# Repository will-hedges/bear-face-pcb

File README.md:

# Cortex Face
 v1 of my QMK-compatible replacement PCB for the Vortex Race 3, hilariously named after my boi

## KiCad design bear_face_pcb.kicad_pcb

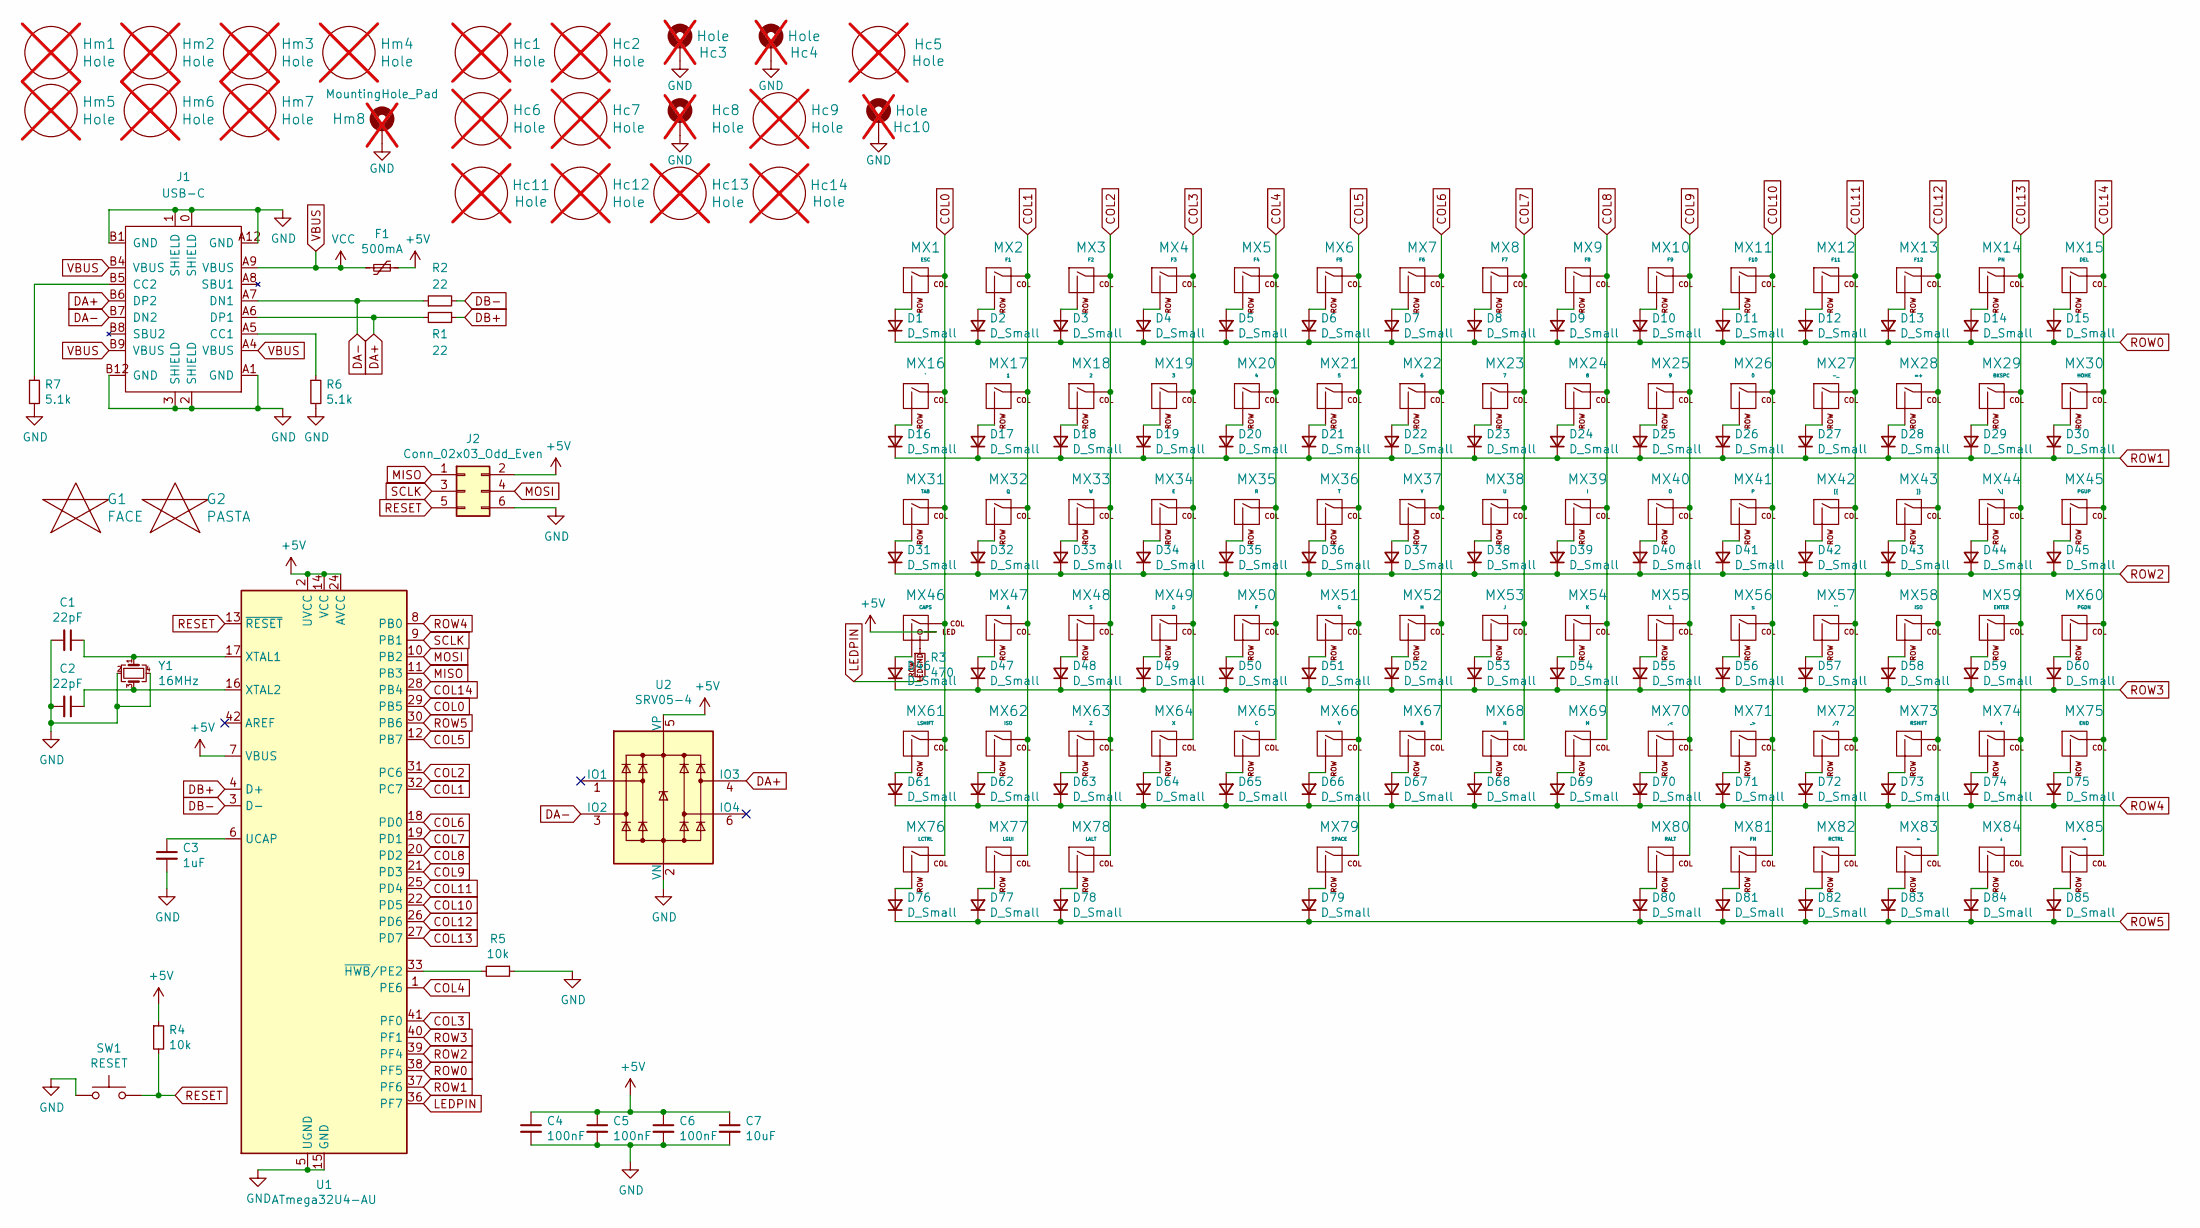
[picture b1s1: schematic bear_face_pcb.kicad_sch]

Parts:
C1, C2: 22pF; C_0805_2012Metric; LCSC C1804
C3: 1uF; C_0805_2012Metric; LCSC C28323
C4, C5, C6: 100nF; C_0805_2012Metric; LCSC C49678
C7: 10uF; C_0805_2012Metric; LCSC C15850
D1, D2, D3, D4, D5, D6, D7, D8, D9, D10, D11, D12, D13, D14, D15, D16, D17, D18, D19, D20, D21, D22, D23, D24, D25, D26, D27, D28, D29, D30, D31, D32, D33, D34, D35, D36, D37, D38, D39, D40, D41, D42, D43, D44, D45, D46, D47, D48, D49, D50, D51, D52, D53, D54, D55, D56, D57, D58, D59, D60, D61, D62, D63, D64, D65, D66, D67, D68, D69, D70, D71, D72, D73, D74, D75, D76, D77, D78, D79, D80, D81, D82, D83, D84, D85: D_Small; D_SOD-123; LCSC C81598
F1: 500mA; Fuse_1206_3216Metric; LCSC C70076
G1: FACE; cbf_small_flipped
G2: PASTA; pasta_small
Hc1, Hc2, Hc5, Hc6, Hc7, Hc9, Hc11, Hc12, Hc13, Hc14: Hole; MountingHole_6mm; not fitted
Hc3, Hc4, Hc8, Hc10: Hole; MountingHole_2.2mm_M2_Pad; not fitted
Hm1, Hm2, Hm3, Hm4, Hm5, Hm6, Hm7: Hole; MountingHole_6mm; not fitted
Hm8: MountingHole_Pad; MountingHole_Header_Pin_Pad; not fitted
J1: USB-C; USB-C_SMD-TYPE-C-31-M-12; LCSC C165948
J2: Conn_02x03_Odd_Even; 2x3pinsocketOFFSET
MX1: ESC; MXOnly-1.5U-NoLED
MX2: F1; MXOnly-1U-NoLED
MX3: F2; MXOnly-1U-NoLED
MX4: F3; MXOnly-1U-NoLED
MX5: F4; MXOnly-1U-NoLED
MX6: F5; MXOnly-1U-NoLED
MX7: F6; MXOnly-1U-NoLED
MX8: F7; MXOnly-1U-NoLED
MX9: F8; MXOnly-1U-NoLED
MX10: F9; MXOnly-1U-NoLED
MX11: F10; MXOnly-1U-NoLED
MX12: F11; MXOnly-1U-NoLED
MX13: F12; MXOnly-1U-NoLED
MX14: PN; MXOnly-1U-NoLED
MX15: DEL; MXOnly-1.5U-NoLED
MX16: `; MXOnly-1U-NoLED
MX17: 1; MXOnly-1U-NoLED
MX18: 2; MXOnly-1U-NoLED
MX19: 3; MXOnly-1U-NoLED
MX20: 4; MXOnly-1U-NoLED
MX21: 5; MXOnly-1U-NoLED
MX22: 6; MXOnly-1U-NoLED
MX23: 7; MXOnly-1U-NoLED
MX24: 8; MXOnly-1U-NoLED
MX25: 9; MXOnly-1U-NoLED
MX26: 0; MXOnly-1U-NoLED
MX27: -_; MXOnly-1U-NoLED
MX28: =+; MXOnly-1U-NoLED
MX29: BKSPC; MXOnly-2U-NoLED
MX30: HOME; MXOnly-1U-NoLED
MX31: TAB; MXOnly-1.5U-NoLED
MX32: Q; MXOnly-1U-NoLED
MX33: W; MXOnly-1U-NoLED
MX34: E; MXOnly-1U-NoLED
MX35: R; MXOnly-1U-NoLED
MX36: T; MXOnly-1U-NoLED
MX37: Y; MXOnly-1U-NoLED
MX38: U; MXOnly-1U-NoLED
MX39: I; MXOnly-1U-NoLED
MX40: O; MXOnly-1U-NoLED
MX41: P; MXOnly-1U-NoLED
MX42: [{; MXOnly-1U-NoLED
MX43: ]}; MXOnly-1U-NoLED
MX44: \|; MXOnly-1.5U-NoLED
MX45: PGUP; MXOnly-1U-NoLED
MX46: CAPS; MXOnly-Stepped-Caps-XD75
MX47: A; MXOnly-1U-NoLED
MX48: S; MXOnly-1U-NoLED
MX49: D; MXOnly-1U-NoLED
MX50: F; MXOnly-1U-NoLED
MX51: G; MXOnly-1U-NoLED
MX52: H; MXOnly-1U-NoLED
MX53: J; MXOnly-1U-NoLED
MX54: K; MXOnly-1U-NoLED
MX55: L; MXOnly-1U-NoLED
MX56: ;:; MXOnly-1U-NoLED
MX57: '"; MXOnly-1U-NoLED
MX58, MX62: ISO; MXOnly-1U-NoLED
MX59: ENTER; MXOnly-ISO-ANSI-Enter-ReversedStabilizers
MX60: PGDN; MXOnly-1U-NoLED
MX61: LSHIFT; MXOnly-Split-LShift
MX63: Z; MXOnly-1U-NoLED
MX64: X; MXOnly-1U-NoLED
MX65: C; MXOnly-1U-NoLED
MX66: V; MXOnly-1U-NoLED
MX67: B; MXOnly-1U-NoLED
MX68: N; MXOnly-1U-NoLED
MX69: M; MXOnly-1U-NoLED
MX70: ,<; MXOnly-1U-NoLED
MX71: .>; MXOnly-1U-NoLED
MX72: /?; MXOnly-1U-NoLED
MX73: RSHIFT; MXOnly-1.75U-NoLED
MX74: ↑; MXOnly-1U-NoLED
MX75: END; MXOnly-1U-NoLED
MX76: LCTRL; MXOnly-1.25U-NoLED
MX77: LGUI; MXOnly-1.25U-NoLED
MX78: LALT; MXOnly-1.25U-NoLED
MX79: SPACE; MXOnly-6.25U-ReversedStabilizers-NoLED
MX80: RALT; MXOnly-1U-NoLED
MX81: FN; MXOnly-1U-NoLED
MX82: RCTRL; MXOnly-1U-NoLED
MX83: ←; MXOnly-1U-NoLED
MX84: ↓; MXOnly-1U-NoLED
MX85: →; MXOnly-1U-NoLED
R1, R2: 22; R_0805_2012Metric; LCSC C17561
R3: 470; R_0805_2012Metric; LCSC C17710
R4, R5: 10k; R_0805_2012Metric; LCSC C17414
R6, R7: 5.1k; R_0805_2012Metric; LCSC C27834
SW1: RESET; 6x6mm_RESET
U1: ATmega32U4-AU; ATMEGA32U4-AU; LCSC C44854
U2: SRV05-4; SOT-23-6; LCSC C85364
Y1: 16MHz; Crystal_SMD_3225-4Pin_3.2x2.5mm; LCSC C13738

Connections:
+5V: C4.1, C5.1, C6.1, C7.1, F1.1, J2.2, MX46.3 (LED), R4.1, U1.2 (UVCC), U1.7 (VBUS), U1.14 (VCC), U1.24 (AVCC), U1.34 (VCC), U1.44 (AVCC), U2.5 (VP)
COL0: MX1.1 (COL), MX16.1 (COL), MX31.1 (COL), MX46.1 (COL), MX61.1 (COL), MX76.1 (COL), U1.29 (PB5)
COL1: MX2.1 (COL), MX17.1 (COL), MX32.1 (COL), MX47.1 (COL), MX62.1 (COL), MX77.1 (COL), U1.32 (PC7)
COL2: MX3.1 (COL), MX18.1 (COL), MX33.1 (COL), MX48.1 (COL), MX63.1 (COL), MX78.1 (COL), U1.31 (PC6)
COL3: MX4.1 (COL), MX19.1 (COL), MX34.1 (COL), MX49.1 (COL), MX64.1 (COL), U1.41 (PF0)
COL4: MX5.1 (COL), MX20.1 (COL), MX35.1 (COL), MX50.1 (COL), MX65.1 (COL), U1.1 (PE6)
COL5: MX6.1 (COL), MX21.1 (COL), MX36.1 (COL), MX51.1 (COL), MX66.1 (COL), MX79.1 (COL), U1.12 (PB7)
COL6: MX7.1 (COL), MX22.1 (COL), MX37.1 (COL), MX52.1 (COL), MX67.1 (COL), U1.18 (PD0)
COL7: MX8.1 (COL), MX23.1 (COL), MX38.1 (COL), MX53.1 (COL), MX68.1 (COL), U1.19 (PD1)
COL8: MX9.1 (COL), MX24.1 (COL), MX39.1 (COL), MX54.1 (COL), MX69.1 (COL), U1.20 (PD2)
COL9: MX10.1 (COL), MX25.1 (COL), MX40.1 (COL), MX55.1 (COL), MX70.1 (COL), MX80.1 (COL), U1.21 (PD3)
COL10: MX11.1 (COL), MX26.1 (COL), MX41.1 (COL), MX56.1 (COL), MX71.1 (COL), MX81.1 (COL), U1.22 (PD5)
COL11: MX12.1 (COL), MX27.1 (COL), MX42.1 (COL), MX57.1 (COL), MX72.1 (COL), MX82.1 (COL), U1.25 (PD4)
COL12: MX13.1 (COL), MX28.1 (COL), MX43.1 (COL), MX58.1 (COL), MX73.1 (COL), MX83.1 (COL), U1.26 (PD6)
COL13: MX14.1 (COL), MX29.1 (COL), MX44.1 (COL), MX59.1 (COL), MX74.1 (COL), MX84.1 (COL), U1.27 (PD7)
COL14: MX15.1 (COL), MX30.1 (COL), MX45.1 (COL), MX60.1 (COL), MX75.1 (COL), MX85.1 (COL), U1.28 (PB4)
DA+: J1.A6 (DP1), J1.B6 (DP2), R1.2, U2.4 (IO3)
DA-: J1.A7 (DN1), J1.B7 (DN2), R2.1, U2.3 (IO2)
DB+: R1.1, U1.4 (D+)
DB-: R2.2, U1.3 (D-)
GND: C1.2, C2.2, C3.2, C4.2, C5.2, C6.2, C7.2, Hc3.1, Hc4.1, Hc8.1, Hc10.1, Hm8.1, J1.0 (SHIELD), J1.1 (SHIELD), J1.2 (SHIELD), J1.3 (SHIELD), J1.A1 (GND), J1.A12 (GND), J1.B1 (GND), J1.B12 (GND), J2.6, R5.1, R6.2, R7.2, SW1.1, U1.5 (UGND), U1.15 (GND), U1.23 (GND), U1.35 (GND), U1.43 (GND), U2.2 (VN), Y1.2, Y1.4
LEDPIN: R3.2, U1.36 (PF7)
MISO: J2.1, U1.11 (PB3)
MOSI: J2.4, U1.10 (PB2)
unnamed: D1.2 (A), MX1.2 (ROW)
unnamed: D2.2 (A), MX2.2 (ROW)
unnamed: D3.2 (A), MX3.2 (ROW)
unnamed: D4.2 (A), MX4.2 (ROW)
unnamed: D5.2 (A), MX5.2 (ROW)
unnamed: D6.2 (A), MX6.2 (ROW)
unnamed: D7.2 (A), MX7.2 (ROW)
unnamed: D8.2 (A), MX8.2 (ROW)
unnamed: D9.2 (A), MX9.2 (ROW)
unnamed: D10.2 (A), MX10.2 (ROW)
unnamed: D11.2 (A), MX11.2 (ROW)
unnamed: D12.2 (A), MX12.2 (ROW)
unnamed: D13.2 (A), MX13.2 (ROW)
unnamed: D14.2 (A), MX14.2 (ROW)
unnamed: D15.2 (A), MX15.2 (ROW)
unnamed: D16.2 (A), MX16.2 (ROW)
unnamed: D17.2 (A), MX17.2 (ROW)
unnamed: D18.2 (A), MX18.2 (ROW)
unnamed: D19.2 (A), MX19.2 (ROW)
unnamed: D20.2 (A), MX20.2 (ROW)
unnamed: D21.2 (A), MX21.2 (ROW)
unnamed: D22.2 (A), MX22.2 (ROW)
unnamed: D23.2 (A), MX23.2 (ROW)
unnamed: D24.2 (A), MX24.2 (ROW)
unnamed: D25.2 (A), MX25.2 (ROW)
unnamed: D26.2 (A), MX26.2 (ROW)
unnamed: D27.2 (A), MX27.2 (ROW)
unnamed: D28.2 (A), MX28.2 (ROW)
unnamed: D29.2 (A), MX29.2 (ROW)
unnamed: D30.2 (A), MX30.2 (ROW)
unnamed: D31.2 (A), MX31.2 (ROW)
unnamed: D32.2 (A), MX32.2 (ROW)
unnamed: D33.2 (A), MX33.2 (ROW)
unnamed: D34.2 (A), MX34.2 (ROW)
unnamed: D35.2 (A), MX35.2 (ROW)
unnamed: D36.2 (A), MX36.2 (ROW)
unnamed: D37.2 (A), MX37.2 (ROW)
unnamed: D38.2 (A), MX38.2 (ROW)
unnamed: D39.2 (A), MX39.2 (ROW)
unnamed: D40.2 (A), MX40.2 (ROW)
unnamed: D41.2 (A), MX41.2 (ROW)
unnamed: D42.2 (A), MX42.2 (ROW)
unnamed: D43.2 (A), MX43.2 (ROW)
unnamed: D44.2 (A), MX44.2 (ROW)
unnamed: D45.2 (A), MX45.2 (ROW)
unnamed: D46.2 (A), MX46.2 (ROW)
unnamed: D47.2 (A), MX47.2 (ROW)
unnamed: D48.2 (A), MX48.2 (ROW)
unnamed: D49.2 (A), MX49.2 (ROW)
unnamed: D50.2 (A), MX50.2 (ROW)
unnamed: D51.2 (A), MX51.2 (ROW)
unnamed: D52.2 (A), MX52.2 (ROW)
unnamed: D53.2 (A), MX53.2 (ROW)
unnamed: D54.2 (A), MX54.2 (ROW)
unnamed: D55.2 (A), MX55.2 (ROW)
unnamed: D56.2 (A), MX56.2 (ROW)
unnamed: D57.2 (A), MX57.2 (ROW)
unnamed: D58.2 (A), MX58.2 (ROW)
unnamed: D59.2 (A), MX59.2 (ROW)
unnamed: D60.2 (A), MX60.2 (ROW)
unnamed: D61.2 (A), MX61.2 (ROW)
unnamed: D62.2 (A), MX62.2 (ROW)
unnamed: D63.2 (A), MX63.2 (ROW)
unnamed: D64.2 (A), MX64.2 (ROW)
unnamed: D65.2 (A), MX65.2 (ROW)
unnamed: D66.2 (A), MX66.2 (ROW)
unnamed: D67.2 (A), MX67.2 (ROW)
unnamed: D68.2 (A), MX68.2 (ROW)
unnamed: D69.2 (A), MX69.2 (ROW)
unnamed: D70.2 (A), MX70.2 (ROW)
unnamed: D71.2 (A), MX71.2 (ROW)
unnamed: D72.2 (A), MX72.2 (ROW)
unnamed: D73.2 (A), MX73.2 (ROW)
unnamed: D74.2 (A), MX74.2 (ROW)
unnamed: D75.2 (A), MX75.2 (ROW)
unnamed: D76.2 (A), MX76.2 (ROW)
unnamed: D77.2 (A), MX77.2 (ROW)
unnamed: D78.2 (A), MX78.2 (ROW)
unnamed: D79.2 (A), MX79.2 (ROW)
unnamed: D80.2 (A), MX80.2 (ROW)
unnamed: D81.2 (A), MX81.2 (ROW)
unnamed: D82.2 (A), MX82.2 (ROW)
unnamed: D83.2 (A), MX83.2 (ROW)
unnamed: D84.2 (A), MX84.2 (ROW)
unnamed: D85.2 (A), MX85.2 (ROW)
unnamed: J1.A5 (CC1), R6.1
unnamed: J1.B5 (CC2), R7.1
unnamed: MX46.4 (LEDGND), R3.1
unnamed: C3.1, U1.6 (UCAP)
unnamed: C1.1, U1.17 (XTAL1), Y1.1
unnamed: C2.1, U1.16 (XTAL2), Y1.3
unnamed: R5.2, U1.33 (~HWB/PE2)
RESET: J2.5, R4.2, SW1.2, U1.13 (~RESET)
ROW0: D1.1 (K), D2.1 (K), D3.1 (K), D4.1 (K), D5.1 (K), D6.1 (K), D7.1 (K), D8.1 (K), D9.1 (K), D10.1 (K), D11.1 (K), D12.1 (K), D13.1 (K), D14.1 (K), D15.1 (K), U1.38 (PF5)
ROW1: D16.1 (K), D17.1 (K), D18.1 (K), D19.1 (K), D20.1 (K), D21.1 (K), D22.1 (K), D23.1 (K), D24.1 (K), D25.1 (K), D26.1 (K), D27.1 (K), D28.1 (K), D29.1 (K), D30.1 (K), U1.37 (PF6)
ROW2: D31.1 (K), D32.1 (K), D33.1 (K), D34.1 (K), D35.1 (K), D36.1 (K), D37.1 (K), D38.1 (K), D39.1 (K), D40.1 (K), D41.1 (K), D42.1 (K), D43.1 (K), D44.1 (K), D45.1 (K), U1.39 (PF4)
ROW3: D46.1 (K), D47.1 (K), D48.1 (K), D49.1 (K), D50.1 (K), D51.1 (K), D52.1 (K), D53.1 (K), D54.1 (K), D55.1 (K), D56.1 (K), D57.1 (K), D58.1 (K), D59.1 (K), D60.1 (K), U1.40 (PF1)
ROW4: D61.1 (K), D62.1 (K), D63.1 (K), D64.1 (K), D65.1 (K), D66.1 (K), D67.1 (K), D68.1 (K), D69.1 (K), D70.1 (K), D71.1 (K), D72.1 (K), D73.1 (K), D74.1 (K), D75.1 (K), U1.8 (PB0)
ROW5: D76.1 (K), D77.1 (K), D78.1 (K), D79.1 (K), D80.1 (K), D81.1 (K), D82.1 (K), D83.1 (K), D84.1 (K), D85.1 (K), U1.30 (PB6)
SCLK: J2.3, U1.9 (PB1)
VBUS: F1.2, J1.A4 (VBUS), J1.A9 (VBUS), J1.B4 (VBUS), J1.B9 (VBUS)

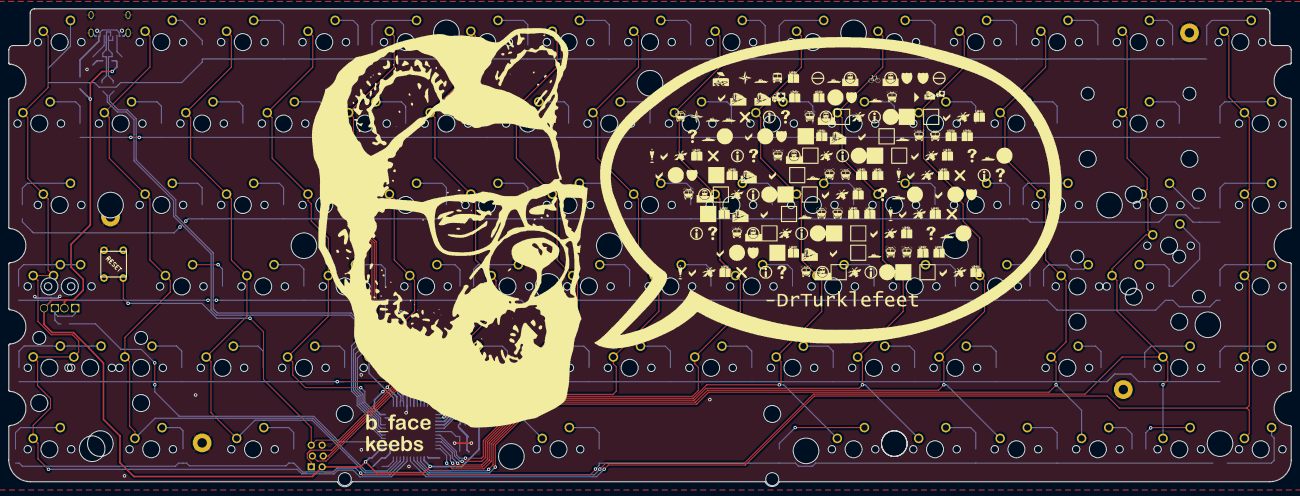
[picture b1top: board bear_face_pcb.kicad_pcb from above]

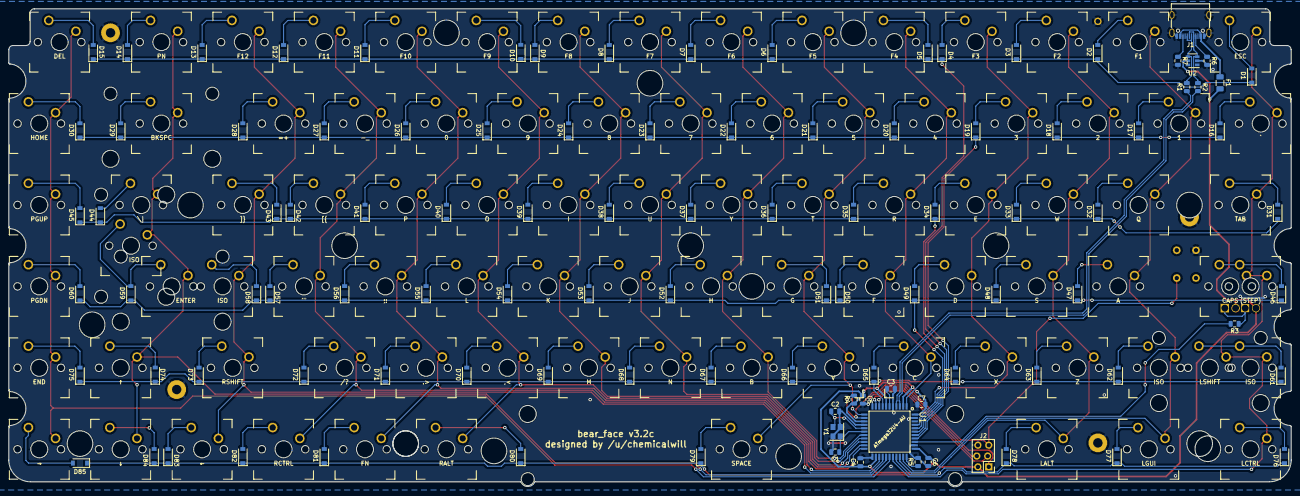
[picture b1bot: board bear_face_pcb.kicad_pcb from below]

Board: 2 copper layers, 300.0 x 111.8 mm, 215 parts (104 on the bottom side), 125 nets.

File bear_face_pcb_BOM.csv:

Comment,Designator,Footprint,LCSC
"22pF","C1,C2","Capacitor_SMD:C_0805_2012Metric","C1804"
"1uF","C3","Capacitor_SMD:C_0805_2012Metric","C28323"
"100nF","C4,C5,C6","Capacitor_SMD:C_0805_2012Metric","C49678"
"10uF","C7","Capacitor_SMD:C_0805_2012Metric","C15850"
"D_Small","D1,D2,D3,D4,D5,D6,D7,D8,D9,D10,D11,D12,D13,D14,D15,D16,D17,D18,D19,D20,D21,D22,D23,D24,D25,D26,D27,D28,D29,D30,D31,D32,D33,D34,D35,D36,D37,D38,D39,D40,D41,D42,D43,D44,D45,D46,D47,D48,D49,D50,D51,D52,D53,D54,D55,D56,D57,D58,D59,D60,D61,D62,D63,D64,D65,D66,D67,D68,D69,D70,D71,D72,D73,D74,D75,D76,D77,D78,D79,D80,D81,D82,D83,D84,D85","Diode_SMD:D_SOD-123","C81598"
"500mA","F1","Fuse:Fuse_1206_3216Metric","C70076"
"FACE","G1","bear_face_silks:cbf_small_flipped",""
"PASTA","G2","bear_face_silks:pasta_small",""
"Hole","H5","bear_face_parts:MountingHole_3mm",""
"Hole","H3,H4,H6,H7,H8,H9,H10","bear_face_parts:MountingHole_6mm",""
"USB_B_Micro-Connector","J1","bear_face_parts:MINI-USB-SMD_MICRO-4P-DIP","C456008"
"Conn_02x03_Odd_Even","J2","bear_face_parts:2x3pinsocketOFFSET",""
"ESC","MX1","bear_face_parts:MXOnly-1.5U-NoLED",""
"F9","MX10","bear_face_parts:MXOnly-1U-NoLED",""
"F10","MX11","bear_face_parts:MXOnly-1U-NoLED",""
"F11","MX12","bear_face_parts:MXOnly-1U-NoLED",""
"F12","MX13","bear_face_parts:MXOnly-1U-NoLED",""
"PN","MX14","bear_face_parts:MXOnly-1U-NoLED",""
"DEL","MX15","bear_face_parts:MXOnly-1.5U-NoLED",""
"`","MX16","bear_face_parts:MXOnly-1U-NoLED",""
"1","MX17","bear_face_parts:MXOnly-1U-NoLED",""
"2","MX18","bear_face_parts:MXOnly-1U-NoLED",""
"3","MX19","bear_face_parts:MXOnly-1U-NoLED",""
"F1","MX2","bear_face_parts:MXOnly-1U-NoLED",""
"4","MX20","bear_face_parts:MXOnly-1U-NoLED",""
"5","MX21","bear_face_parts:MXOnly-1U-NoLED",""
"6","MX22","bear_face_parts:MXOnly-1U-NoLED",""
"7","MX23","bear_face_parts:MXOnly-1U-NoLED",""
"8","MX24","bear_face_parts:MXOnly-1U-NoLED",""
"9","MX25","bear_face_parts:MXOnly-1U-NoLED",""
"0","MX26","bear_face_parts:MXOnly-1U-NoLED",""
"-_","MX27","bear_face_parts:MXOnly-1U-NoLED",""
"=+","MX28","bear_face_parts:MXOnly-1U-NoLED",""
"BKSPC","MX29","bear_face_parts:MXOnly-2U-NoLED",""
"F2","MX3","bear_face_parts:MXOnly-1U-NoLED",""
"HOME","MX30","bear_face_parts:MXOnly-1U-NoLED",""
"TAB","MX31","bear_face_parts:MXOnly-1.5U-NoLED",""
"Q","MX32","bear_face_parts:MXOnly-1U-NoLED",""
"W","MX33","bear_face_parts:MXOnly-1U-NoLED",""
"E","MX34","bear_face_parts:MXOnly-1U-NoLED",""
"R","MX35","bear_face_parts:MXOnly-1U-NoLED",""
"T","MX36","bear_face_parts:MXOnly-1U-NoLED",""
"Y","MX37","bear_face_parts:MXOnly-1U-NoLED",""
"U","MX38","bear_face_parts:MXOnly-1U-NoLED",""
"I","MX39","bear_face_parts:MXOnly-1U-NoLED",""
"F3","MX4","bear_face_parts:MXOnly-1U-NoLED",""
"O","MX40","bear_face_parts:MXOnly-1U-NoLED",""
"P","MX41","bear_face_parts:MXOnly-1U-NoLED",""
"[{","MX42","bear_face_parts:MXOnly-1U-NoLED",""
"]}","MX43","bear_face_parts:MXOnly-1U-NoLED",""
"\|","MX44","bear_face_parts:MXOnly-1.5U-NoLED",""
"PGUP","MX45","bear_face_parts:MXOnly-1U-NoLED",""
"CAPS","MX46","bear_face_parts:MXOnly-Stepped-Caps-XD75",""
"A","MX47","bear_face_parts:MXOnly-1U-NoLED",""
"S","MX48","bear_face_parts:MXOnly-1U-NoLED",""
"D","MX49","bear_face_parts:MXOnly-1U-NoLED",""
"F4","MX5","bear_face_parts:MXOnly-1U-NoLED",""
"F","MX50","bear_face_parts:MXOnly-1U-NoLED",""
"G","MX51","bear_face_parts:MXOnly-1U-NoLED",""
"H","MX52","bear_face_parts:MXOnly-1U-NoLED",""
"J","MX53","bear_face_parts:MXOnly-1U-NoLED",""
"K","MX54","bear_face_parts:MXOnly-1U-NoLED",""
"L","MX55","bear_face_parts:MXOnly-1U-NoLED",""
";:","MX56","bear_face_parts:MXOnly-1U-NoLED",""
"'"","MX57","bear_face_parts:MXOnly-1U-NoLED",""
"ENTER","MX59","bear_face_parts:MXOnly-ISO-ANSI-Enter-ReversedStabilizers",""
"F5","MX6","bear_face_parts:MXOnly-1U-NoLED",""
"PGDN","MX60","bear_face_parts:MXOnly-1U-NoLED",""
"LSHIFT","MX61","bear_face_parts:MXOnly-Split-LShift",""
"ISO","MX58,MX62","bear_face_parts:MXOnly-1U-NoLED",""
"Z","MX63","bear_face_parts:MXOnly-1U-NoLED",""
"X","MX64","bear_face_parts:MXOnly-1U-NoLED",""
"C","MX65","bear_face_parts:MXOnly-1U-NoLED",""
"V","MX66","bear_face_parts:MXOnly-1U-NoLED",""
"B","MX67","bear_face_parts:MXOnly-1U-NoLED",""
"N","MX68","bear_face_parts:MXOnly-1U-NoLED",""
"M","MX69","bear_face_parts:MXOnly-1U-NoLED",""
"F6","MX7","bear_face_parts:MXOnly-1U-NoLED",""
",<","MX70","bear_face_parts:MXOnly-1U-NoLED",""
".>","MX71","bear_face_parts:MXOnly-1U-NoLED",""
"/?","MX72","bear_face_parts:MXOnly-1U-NoLED",""
"RSHIFT","MX73","bear_face_parts:MXOnly-1.75U-NoLED",""
"↑","MX74","bear_face_parts:MXOnly-1U-NoLED",""
"END","MX75","bear_face_parts:MXOnly-1U-NoLED",""
"LCTRL","MX76","bear_face_parts:MXOnly-1.25U-NoLED",""
"LGUI","MX77","bear_face_parts:MXOnly-1.25U-NoLED",""
"LALT","MX78","bear_face_parts:MXOnly-1.25U-NoLED",""
"SPACE","MX79","bear_face_parts:MXOnly-6.25U-ReversedStabilizers-NoLED",""
"F7","MX8","bear_face_parts:MXOnly-1U-NoLED",""
"RALT","MX80","bear_face_parts:MXOnly-1U-NoLED",""
"FN","MX81","bear_face_parts:MXOnly-1U-NoLED",""
"RCTRL","MX82","bear_face_parts:MXOnly-1U-NoLED",""
"←","MX83","bear_face_parts:MXOnly-1U-NoLED",""
"↓","MX84","bear_face_parts:MXOnly-1U-NoLED",""
"→","MX85","bear_face_parts:MXOnly-1U-NoLED",""
"F8","MX9","bear_face_parts:MXOnly-1U-NoLED",""
"22","R1,R2","Resistor_SMD:R_0805_2012Metric","C17561"
"470","R3","Resistor_SMD:R_0805_2012Metric","C17710"
"10k","R4,R5","Resistor_SMD:R_0805_2012Metric","C17414"
"RESET","SW1","bear_face_parts:6x6mm_RESET",""
"ATmega32U4-AU","U1","bear_face_parts:ATMEGA32U4-AU","C44854"
"SRV05-4","U2","Package_TO_SOT_SMD:SOT-23-6","C85364"
"16MHz","Y1","Crystal:Crystal_SMD_3225-4Pin_3.2x2.5mm","C13738"

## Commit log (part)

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2019-12-10 Add submodules
2019-12-10 symbol and footprint libraries added
    added symbol and footprint libraries for ai03's MX-Alps Hybrid and random keyboard parts
2019-12-10 MCU schematic for 32u4
    Completed MCU zone on schematic for ATmega32u4 controller
2019-12-12 Annotated schematic
    Annotated schematic without any assigned footprints
2019-12-12 Footprints assigned
    Footprints (including non-standard key sizes) assigned using MX-Alps Hybrid submodule
2019-12-16 Added Pro Micro libary + footprint
2019-12-17 Pro Micro and USB JCON powered
2019-12-17 10x9 layout
    Changed switch matrix to 10x9 (columns x rows) to use fewer pins
2019-12-18 PCB started
    Footprints defined
2019-12-18 Changed footprints
    Changed switch footprints to MX Only, no LED
2019-12-18 Changed footprints
    Footprints for non-standard switch sizes updated
2019-12-19 Diodes placed
2019-12-19 USB and J conn placed
2019-12-19 Fixed 5V power to Elite-C
2019-12-23 Autorouted
    Using FreeRouting
2019-12-23 Tweaked routing
    Changed routing around the USB and Elite-C
2019-12-23 Edge Cuts & DRC Errors Fixed
2019-12-27 Updated footprints
    Changed to USB micro for drop-in compatibility, changed connector wire size. No DRC errors.
2019-12-28 Re-traced
    Removed auto-traced pcb, all manual tracings. Removed submodules not used.
2019-12-28 Tracing, footprints, submodules updated
    Re-traced by hand, updated several footprints and spacings, removed unused submodules.
2019-12-28 Removed footprints
    Removed bluepill footprints
2019-12-30 Sizing/Edge Cut Adjustments
    Re-measured PCB and cut down PCB accordingly. Changed holes on edges to edge cuts
2020-01-04 Track edits
    Edited tracks around USB and J1 connector to cross at right angles, cleaned up tracks to GND and Reset at IC
2020-01-05 Naming updated
    Numbered switches rather than keep QWERTY labels
2020-01-06 Massive update
    Changed names to Bear Face 1, moved Elite-C to under the spacebar & updated tracks as necessary. Need to check mounting hole positions, but other than that almost ready for gerbers
2020-01-07 Conflicts resolved
    Resolved git conflicts due to name changes (tracks updated)
2020-01-07 Elite-C moved
    Updated schematic, PCB to reflect Elite-C position change to under spacebar
2020-01-07 Mounting holes updated
    Used caliper to measure mounting holes on stock PCB, moved mounting holes and surrounding tracks for better fit.
2020-01-07 Added hole for plate ground
    Stock plate has a hole grounding the plate to the PCB. Added this hole as a 3mm mounting hole (H8)
2020-01-07 Moved USB connector
    Re-measured and moved USB connector to be closer to stock PCB
2020-01-07 Added matrix drawing
    Matrix drawing uploaded for clarity
2020-01-07 Tracks and vias cleaned up
    Ran and cleaned up tracks and vias, DRC check clear
2020-01-08 SilkS added
    Decoration
2020-01-14 Matrix, footprints changed
    Changed to pure rectangular matrix, updated switch and diode SilkS, anticipate using on-board 32u4
2020-01-14 MCU added, diodes changed
    Changed to SMD components, matched components used in ai03's guide
2020-01-14 Diode footprints updated, MCU components started
2020-01-14 Short diode tracks added
2020-01-14 Row tracks drawn
2020-01-15 Columns drawn in
    Ignore differential pair - going to take some work
2020-01-15 Fixed dPair, USB connector schematic
2020-01-15 Track tweaks
2020-01-15 MCU tracks done
    All tracks done except for switch matrix
2020-01-15 MCU tracks complete
    5V no longer running under MCU, all GNDs and 5V nets tied in.
2020-01-16 Edge issues fixed
    Moved MCU tracks, diodes to be at least 1mm from pcb edge
2020-01-16 Footprints updated, minor track tweaks
    Removed solder mask on switch leg holes
2020-01-16 SilkS added
    Goofy ass inside jokes added to an otherwise sexy board
2020-01-16 Diode SilkS flipped
    Flipped diode silkscreen to show up rather than be covered up by graphics
2020-01-16 Stiching via footprint added
    Added 0.6mm stitching via footprint from https://forum.kicad.info/t/protip-nicer-via-stitching/1103
2020-01-16 Made copies of edited footprints
2020-01-16 DRC check
    DRC check after adding/removing stitching vias, flipping diode SilkS, and small visual tweaks
2020-01-16 Renamed files
    Renamed all files from "Bear-Face-1" to "bear_face"
2020-01-16 Initial SMD commit
    Diodes changed to SMD, short tracks added to pad2 and between adjacent diodes
2020-01-16 Rows, MCU caps and resistors tracked
2020-01-16 Changed RESET switch to SMD
2020-01-16 dPairs, left side MCU tracked
2020-01-16 Tracks finished, DRC check passed, tracks and vias cleaned up
2020-01-16 Reconnected USB GND to SW1
    Minor tracking tweaks, DRC check passed
2020-01-17 Footprints updated
    Moved MX footprint outlines to back SilkS
2020-01-18 Added GND fill to front of PCB
2020-01-18 Resistors moved
    Resistors moved out of the MX footprint silkscreen
2020-01-18 Footprints updated
    Removed No-LED footprints, moved Ref on mx footprints
2020-01-18 Minor sch tweaks for MOSFET
2020-01-18 Short traces flipped
    Flipped short trace from LED to resistor to B.Cu
2020-01-18 Rows mostly drawn
2020-01-18 DRC checked, tracks updated
2020-01-18 Changed MCU components back to SMD
2020-01-19 USB track drawn first
    Tracks wiped, footprints for resistors shrunk down, USB tracks drawn first
2020-01-22 AVR ISP pins added, routed
2020-01-22 Routed traces crossing dPair
    Traces expected to cross dPair routed at 90 degree angles
2020-01-22 Started column routing
2020-01-22 Columns routed
2020-01-22 Switch resistors routed
    finished per-switch resistor routing
2020-01-23 LEDOUT net routed on rows
2020-01-23 LEDOUT net tied together
    not yet connected to MOSFET
2020-01-23 +5V net tied in, matrix started
2020-01-24 Initial branch commit
    LED only for Caps Lock, updated footprints
2020-01-25 MCU components routed
2020-01-25 dPair routed
2020-01-25 Rows routed
2020-01-25 Routing tweaks
2020-01-25 Updated ESD tracking, edited footprints
    Caps key footprint LED pads now support xd75 hotswap LED sockets
2020-01-25 All nets routed, GND fill stitched, DRC passed
    Ready for gerbers
2020-01-26 Decoration added
2020-01-26 Added decorations to .sch
    No longer wiped by update from .sch
2020-01-26 LCSC#s added to schematic
    C codes added for SMT assembly pick and place
2020-01-26 ESD chip moved south, edge cuts fixed, minor SilkS tweaks
    ESD moved for sake of easier hand soldering of micro USB
2020-02-12 BOM, .pos, Gerbers added
2020-02-18 SilkS moved, Gerbers reuploaded
    Centered deco + replaced gerbers
2020-02-18 Helper script files added
2020-02-20 Edge cuts, mounting holes cleaned up
    Moved edges, holes to better match stock PCB. Refilled GND and DRC passed
2020-02-24 Mounting holes, USB moved
    Updated mouting holes and USB position after adjusting edge cuts
2020-02-24 GND traces removed and connected to GND fill
2020-02-24 Removed .DSN for autorouting
    Removing old files
2020-02-24 Removed old files
    Added to .gitignore
2020-02-24 USB GND routed directly to ESD
    Now grounded to fill and via trace
2020-02-24 GND fill, tracks cleaned up, DRC passed
2020-02-24 Gerbers re-done
    Final gerbers ready for production
2020-02-24 .pos, BOM, JLCKicadTools files added
    For use with JLC SMT assembly service
2020-03-19 Added layout image
2020-05-27 Added optional stepped Caps Lock support
    * Same spot in the matrix, traced to allow either switch position
2020-05-28 Added ISO Enter support
    * ISO enter shares a matrix position with ANSI \|
2020-05-28 Fixed ISO left shift, matrix and tracks changed
    * shifted Row 4 by 1 unit to the right to accomodate split left shift
2020-05-28 Tracking tweaks
    * minor track cleanup
2020-05-29 Fixed ISO footprints, relabeled switch SilkS
2020-05-29 Minor SilkS tweaks, tracks and vias cleaned up
2020-05-29 GND fill tweaked
2020-05-29 Changed ISO matrix to better match other boards
    * ISO and ANSI enter now share matrix pos
    * ISO keys moved to own matrix pos where possible
2020-05-29 Tracks cleaned up, GND fill improved
2020-05-29 SilkS, mask changes
    * removed mask from pads on new footprints
2020-05-29 Minor tweaks
2020-05-29 More minor tweaks
2020-05-29 Reverted RESET switch to through-hole
    * cannot use JLC assembly with SMD parts on multiple sides
    * prefer through-hole for switches
2020-05-29 Gerbers, Drill files added for v2
2020-05-29 Renamed files from 'bear_face' to 'bear_face_pcb' for jlc-kicad-tools ease
    * issues with repo name and file names
2020-05-31 Renamed gerber files to 'bear_face_pcb'
2020-05-31 Added gerber zip, jlc-kicad-tools files
2020-06-02 Changed LCSC# for crystal
    Now basic part
2020-06-02 New gerbers
2020-12-04 Initial commit for v2.1
    * connected case plate hole to GND
    * silkS now says 2.1
2021-02-11 More track tweaks
    Removed 90 deg tracks
2021-02-13 Fixed more 90 deg tracks, unconnected GND fills
2021-02-14 Changed ISO Enter SilkS, added new gerbers
    * not yet run jlc script
2021-03-11 New BOM and .pos, just in case
2021-03-11 Renamed gerbers, ISO silkS tweak, new bom and cpl
2021-03-11 Changed hand-solder pads to... not hand-solder
2021-07-10 Refilled zones, re-checked DRC
2021-07-10 Set solder mask values to 0
2023-02-28 initial branch commit * very dirty - lots of overlapping traces * removed MOSFET * replaced diode footprints * WIP commit for remote storage
2023-03-04 finished flipping row2 * began flipping row3 * flipped 5V rail to front Cu layer
2023-03-30 finished tracking for all SMD version
2023-11-05 new BOM, gerbers
2023-11-06 changed USB footprint, updated BOM, gerbers FINAL
2023-11-06 initial USB-C commit
2023-11-06 numbering tweaks, grounded pcb to plate hole, silks edit
2023-11-06 ready for JLC, routing/place tweaks
2023-11-08 cleanup tracks, GND vias
2023-11-08 replaced usb micro
2023-11-08 pulled up to v3c route/via changes + * replaced micro usb * placed components for diff pairs
2023-11-10 standardized footprints, moved USB, moved silks * 'professionalized' * deleted old gerbers * RESET switch looks much nicer
2023-11-10 changed USB footprint
2023-11-11 initial footprint changes
2023-11-11 inital stab placement * deleted no stab footprints * updated footprints for readability
2023-11-12 initial reroute complete * BSLS key may be an issue * DRC all connected, usual warnings seen
2023-11-12 rotated ISO enter 90 degrees * fixed routing, GND fill
2023-11-13 moved mounting hole near spacebar
2023-11-22 cleaned up RESET silks
2023-11-23 renumbered Resistors
2023-11-24 final silks tweaks, final gerbers
2023-11-27 lined up mounting holes with plate holes * now based off coords * may need to make an edge footprint * not wild about one edge being so close * TODO change H5 to pad * NOTE renumbered holes
2023-12-01 tweaked edge cuts for silkscreen
2023-12-02 added S edge gnd via
2023-12-09 relabeled BOM file
2023-12-09 new gerbers w/ updated silks
2023-12-11 minor logo, text silks tweaks * plus new gerbers
2023-12-11 changed diodes to SOD-123 * removed old gerbers, .pos, BOM
2023-12-11 diode silks tweaks
2023-12-11 initial branch commit
2023-12-11 placed USB-C components, traces * new gerbers
2023-12-11 new BOM, pos, gerbers
2024-01-19 added top corner cutouts * moved D1
2024-01-19 grounded plate mount * old footprint was not actually grounded * denoted versioning as v3.1c
2024-01-19 grounded plate ground * never changed old footprint * updated version to v3.1 on silks
2024-01-19 updated .gitignore
2024-01-19 removed #auto_saved_files#
2024-01-19 .gitignore now working
2024-01-19 changing mount holes to unplated WIP
2024-01-19 plate ground, fmask changes * still need to round corners * need new gerbers
2024-01-19 added fp-info-cache to .gitignore
2024-01-20 repo cleanup in favor of JLC plugin
2024-01-23 moved MCU up to make board smaller * major routing overhaul * stabilized spacebar stab mounts
2024-01-24 minor track, gnd, silk tweaks * technically v3.1c since other 3.1c never printed * will change branch name if protos ok * .gitignore now working
2024-01-24 minor track tweaks
2024-01-24 better marked USB port location
2024-01-24 rounded stab area pcb, new gerbers, minor silks tweaks
2024-01-24 renamed gerber zip
2026-03-25 fixed spacebar stabilizer holes * bottom-edge stabilizer holes should not need to be filed down now * generated new gerbers (not tested)
